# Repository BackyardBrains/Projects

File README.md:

# Projects

Backyard Brains hosts experiment development projects throughout the year. Some of these turn into our experiments, some of these are for our own intellectual curiosity, and some turn into publications in peer reviewed journals. Here you will find each project which contains our open-source schematics, docs, and code.

The projects are:

 * Songbird - A device that can collect environmental and geo-positioning data while detecting and identifying birdsongs automatically.

 * Electric Fish - A collection of projects designed around the recording and micro-stimulation of weakly electric fish. For electric fish that produce "spikes", we are developing a long-term recording device to listen for spiking activity and record the waveforms at highspeed.  For "wave" electric fish, we are developing a device that listens to the frequency of the electric fish, and to initiate a jamming avoidance response by adding an artifical fish in the water next to it that emits a frequency similar to the fish.

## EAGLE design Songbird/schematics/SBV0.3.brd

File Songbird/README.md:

# Songbird project

## Background 

Climate change is affecting all of the natural world, and the habitat and survival of many species of birds are being threatened. In order to understand the effects of climate change on birds, it is crucial to record and track songbird activity. The goal of this project is to develop a system that can correctly identify the songs of eight common and local birds of Michigan. This device will record the bird song and relevant environmental information, such as start time, end time, and location. In doing so, we must consider and further define our goals for power usage, connectivity, longevity, and cost. Our ultimate goal is to create a product that can automatically report this data and is suitable for deployment in nature spanning weeks or months. Our highest level stakeholder, Backyard Brains, hopes that their investment will help us learn more about the behavior of songbirds and the broader implications of climate change.

## Early Research and Results

There are many different types of recording devices that field ornithologists use to record songs and calls, as well as existing algorithms that automatically recognize and identify songs. Based on research into relevant literature, there seem to be many different projects that cover this topic, but our device will be unique in execution. As of now, we plan to either upcycle phones or create our own devices to be placed in the field that will record bird songs.This data will then be processed by the device or stored for processing post recording. Machine learning techniques have shown to be very successful in identifying birds. We have also explored the ideas of using pitch and timbre data and the difference between calls and songs to help us identify bird species. Some challenges that we may face include noise interference, file storage, and durability of the recording devices.

## Impact of Success 

This project is important to our sponsor because bird song and communication is applicable to the field of neuroscience, and birdsongs can tell us much about their behavior. Additionally, Backyard Brains is a company focused on educational outreach, and this project is a good way of educating the public on bird behavior, climate change, and how they can be a part of data collection for research. More broadly, this is important for ornithologists and ecologists because the project provides an accessible and effective device that can provide insight into the patterns of bird populations. Researchers will be able to use this data to use for further studies in understanding the effects of climate change. The device will not be limited to scientists, but be available to the public as well as a way to be involved in community science.

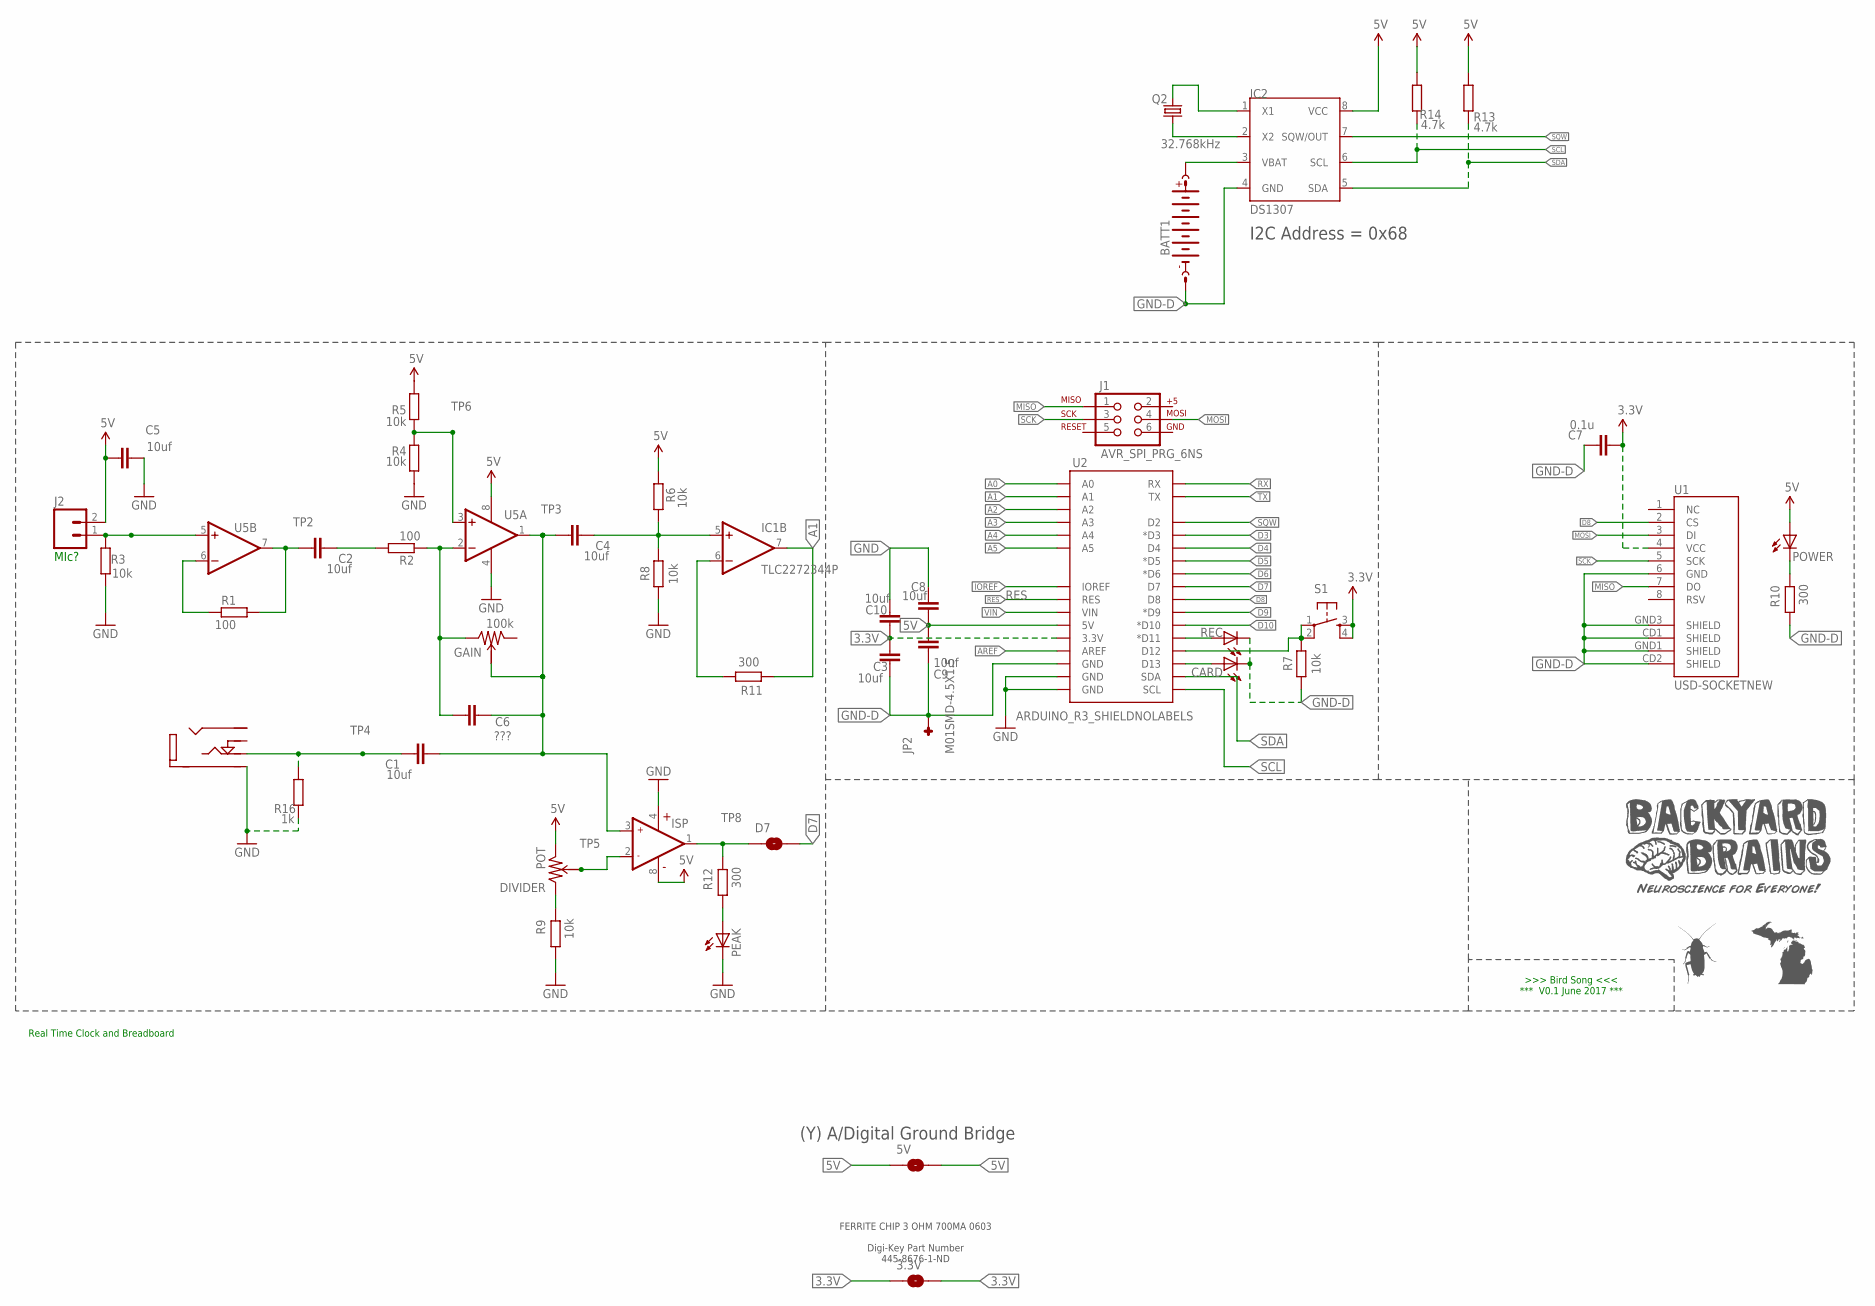
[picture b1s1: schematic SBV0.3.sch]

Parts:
3.3V, 5V: SOLDERJUMPERTRACE; SJ_2S-TRACE
BATT1: BATTERY-16MMSMD; 16M_BATT_SMD
C1, C2, C3, C4, C5, C8, C9, C10: 10uf; M2-CAP; PARTNO K474Z20Y5VE5TL2; DIGIKEY BC1150CT-ND
C6: ???; M2-CAP; PARTNO K474Z20Y5VE5TL2; DIGIKEY BC1150CT-ND
C7: 0.1u; M2-CAP; PARTNO K474Z20Y5VE5TL2; DIGIKEY BC1150CT-ND
CARD: LED5MM
D7: SOLDERJUMPERTRACE; SJ_2S-TRACE
DIVIDER: POT; BURNS-SCREW-POT
GAIN: 100k; BURNS-SCREW-POT
IC1: TLC2272344P; DIL08
IC2: DS1307; DIL08
J1: AVR_SPI_PRG_6NS; 2X3-NS
J2: M02PTH; 1X02
J3: AUDIOJACK; 3.5MM-SMALL-JACK-NEW
JP2: M01SMD-4.5X1.5; PAD-1.5X4.5
PEAK: LED5MM
POWER: LED5MM
Q2: 32.768kHz; TC26H
R1, R2: 100; 0309V; PARTNO CF14JT390R; DIGIKEY CF14JT390RCT-ND
R3, R6, R7, R8: 10k; 0309V; PARTNO ERD-S2TJ102V; DIGIKEY P1.0KBACT-ND
R4, R5, R9: 10k; 0309V; PARTNO CF14JT390R; DIGIKEY CF14JT390RCT-ND
R10, R12: 300; 0309V; PARTNO CF14JT390R; DIGIKEY CF14JT390RCT-ND
R11: 300; 0309V; PARTNO ERD-S2TJ102V; DIGIKEY P1.0KBACT-ND
R13, R14: 4.7k; 0309V; PARTNO ERD-S2TJ102V; DIGIKEY P1.0KBACT-ND
R16: 1k; 0309V; PARTNO ERD-S2TJ102V; DIGIKEY P1.0KBACT-ND
REC: LED5MM
S1: TAC_SWITCHPTH; TACTILE-PTH
TP1, TP2, TP3, TP4, TP5, TP6, TP8: TEST; PROBE_TP
U1: USD-SOCKETNEW; MICRO-SD-SOCKET-PP
U2: ARDUINO_R3_SHIELDNOLABELS; UNO_R3_SHIELD_NOLABELS
U5: TLC2272344P; DIL08; PARTNO TLC2272CP; DIGIKEY 296-1812-5-ND

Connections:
3.3V: 3.3V.1, 3.3V.2, C3.1, C7.1, C10.1, S1.3, S1.4, U1.4 (VCC), U2.3.3V
5V: 5V.1, 5V.2, C5.1, C8.2, C9.2, DIVIDER.1, IC1.8 (V+), IC2.8 (VCC), J2.2, POWER.A, R5.2, R6.1, R13.2, R14.2, U2.5V, U5.8 (V+)
A0: U2.A0
A1: IC1.7 (OUT), R11.2, U2.A1
A2: U2.A2
A3: U2.A3
A4: U2.A4
A5: U2.A5
AMP2: C2.1, R1.2, TP2.P$1, U5.7 (OUT)
AREF: U2.AREF
ASD: D7.1, IC1.1 (OUT), R12.1, TP8.P$1
D3: U2.D3 (*D3)
D4: U2.D4
D5: U2.D5 (*D5)
D6: U2.D6 (*D6)
D7: D7.2, U2.D7
D8: U1.2 (CS), U2.D8
D9: U2.D9 (*D9)
D10: U2.D10 (*D10)
FILTER: C1.1, C4.1, C6.2, GAIN.2, IC1.3 (IN+), TP3.P$1, U5.1 (OUT)
GND: C5.2, C8.1, C10.2, IC1.4 (V-), J3.SHIELD, PEAK.K (C), R3.1, R4.1, R8.2, R9.2, R16.1, U2.GND@0 (GND), U2.GND@1 (GND), U5.4 (V-)
GND-D: BATT1.NEG (-), C3.2, C7.2, C9.1, CARD.K (C), IC2.4 (GND), JP2.P$1, R7.2, R10.2, REC.K (C), U1.6 (GND), U1.CD1 (SHIELD), U1.CD2 (SHIELD), U1.GND1 (SHIELD), U1.GND3 (SHIELD), U2.GND@2 (GND)
IOREF: U2.IOREF
MISO: J1.1, U1.7 (DO)
MOSI: J1.4, U1.3 (DI)
unnamed: J2.1, R3.2, TP1.P$1, U5.5 (+IN)
unnamed: REC.A, U2.D11 (*D11)
unnamed: R1.1, U5.6 (-IN)
unnamed: C2.2, R2.2
unnamed: R4.2, R5.1, TP6.P$1, U5.3 (+IN)
unnamed: POWER.K (C), R10.1
unnamed: DIVIDER.3, R9.1
unnamed: IC2.1 (X1), Q2.2
unnamed: IC1.6 (-IN), R11.1
unnamed: IC2.2 (X2), Q2.1
unnamed: DIVIDER.2, IC1.2 (IN-), TP5.P$1
unnamed: R7.1, S1.1, S1.2, U2.D12
unnamed: CARD.A, U2.D13
unnamed: PEAK.A, R12.2
unnamed: BATT1.POS1 (+), BATT1.POS2 (+), IC2.3 (VBAT)
unnamed: C1.2, J3.R, R16.2, TP4.P$1
unnamed: C6.1, GAIN.3, R2.1, U5.2 (-IN)
PREA1: C4.2, IC1.5 (+IN), R6.2, R8.1
RES: U2.RES
RX: U2.RX
SCK: J1.3, U1.5 (SCK)
SCL: IC2.6 (SCL), R14.1, U2.SCL
SDA: IC2.5 (SDA), R13.1, U2.SDA
SQW: IC2.7 (SQW/OUT), U2.D2
TX: U2.TX
VIN: U2.VIN

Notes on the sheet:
MIc?
I2C Address = 0x68
Real Time Clock and Breadboard
FERRITE CHIP 3 OHM 700MA 0603 Digi-Key Part Number 445-8676-1-ND
(Y) A/Digital Ground Bridge

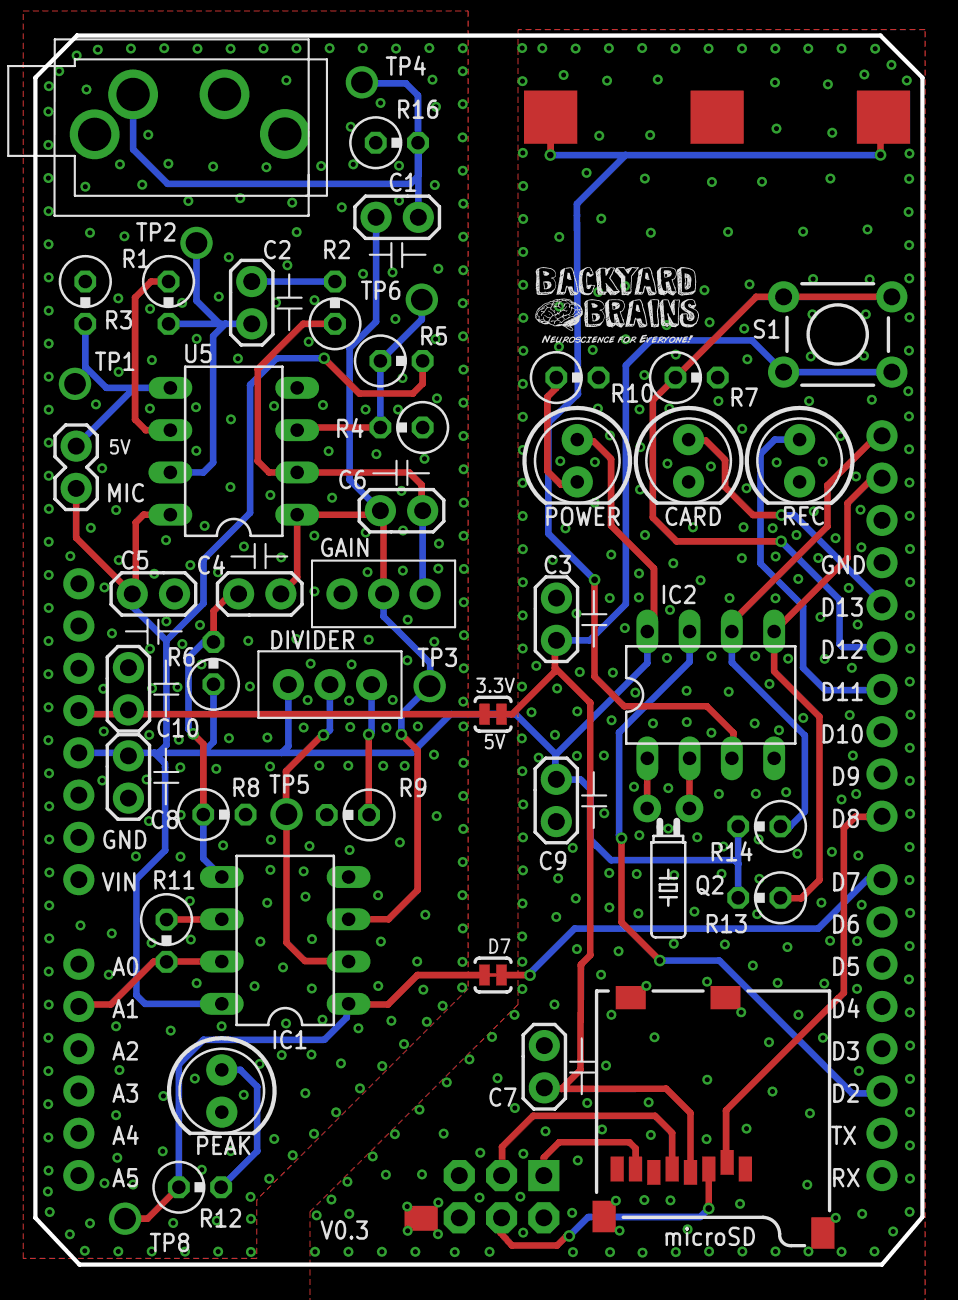
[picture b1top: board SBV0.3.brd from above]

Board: 2 copper layers, 53.3 x 73.9 mm, 54 parts (1 on the bottom side), 34 nets.

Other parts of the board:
U$1: LOGO-NEW-SMALL

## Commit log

2017-02-01 Songbird dir added
2017-02-03 Old projects added to Archive
2017-02-06 Added Directories
2017-02-06 Adding Directores
2017-02-06 Update README.md
    Added descriptions
2017-02-07 Added Electric Fish projects to readme
2017-02-07 Added electric fish descriptions.
2017-02-11 Added files for testing pyaudioanalysis
2017-02-17 added more testing statistics
2017-02-20 fixed divide by zero bug
2017-02-22 unicode fix
2017-02-23 created noise removal function
2017-02-25 added noise removal for entire directory recursively
2017-03-05 database...
2017-03-05 updated database
2017-03-11 logo
2017-03-11 database update to the species and percentage and the variable types
2017-03-11 buttons
2017-03-13 button style
2017-03-13 controllers
2017-03-13 get request and op
2017-03-13 options
2017-03-13 100 lines of random data
2017-03-13 edits
2017-03-13 type not long enough
2017-03-13 data
2017-03-13 changes to get rid of indent?
2017-03-13 quotes
2017-03-14 vagrant
2017-03-15 deleted vagrant
2017-03-15 output precision and style updates
2017-03-15 relative picture size
2017-03-15 more updates
2017-03-21 updates to app layout for easier use/navigation
2017-03-21 added to web app
2017-03-21 got rid of path
2017-03-22 web app update
2017-03-22 navbar
2017-03-22 main is done!
2017-03-28 changed directory name convention to avoid confusion for categorization
2017-03-29 Reverted changes in main.py and index.html, then added other sections. Added working sqlpage. Will need to do input sanitization later to prevent database modifications.
2017-03-29 git ignore
2017-03-29 Sanitized sql command input for sqlpage.
2017-03-29 slight improvements to noise_removal
2017-03-30 basic implementation for processing on device
2017-03-30 bug fixes
2017-03-31 updated for compatability with new version of pysox
2017-04-01 bug fix
2017-04-02 added sanitize, slight tweak to error message in noise_removal
2017-04-02 testing protocol updates
2017-04-02 added sanitize to testing
2017-04-05 updates to web app
2017-04-05 moved css style so that it covers the main page table too
2017-04-05 added categorize file, parrellelized noisered
2017-04-06 bug fix for version mismatch on device
2017-04-06 typo
2017-04-06 compatablity
2017-04-06 device compatability
2017-04-06 added skip-clean option to clean and test and fixed model name bug
2017-04-08 added no-sanitize option
2017-04-09 Added on-device classifier to create sql files to import into live server
2017-04-13 classifier updates
2017-04-18 database folder has been deleted and moved to bybsongbird repository
2017-04-18 added single file classify
2017-04-18 added current model
2017-04-26 parallel classifier v1
2017-04-27 parallelized testing procedure
2017-04-27 added choose number of threads option to objects
2017-04-27 added number of threads option to command line for classifier
2017-05-18 error handling in noise reduce
2017-05-30 some stats analysis
2017-05-31 stats
2017-05-31 test cases
2017-05-31 individual roc curve plotting and auc (hopefully)
2017-05-31 auc should be correct, but don't have graphing yet
2017-05-31 have individual aucs and macro-averaged auc, no curve plotting yet
2017-05-31 possibly all auc measures?
2017-05-31 started realtime recording
2017-06-02 handle weird error
2017-06-04 multithreading workaround for pi zero
2017-06-04 quick noise reduction fix
2017-06-04 error handling
2017-06-04 debug and non-debug for file processing
2017-06-04 fs error fix
2017-06-19 New project for sleep EEG and memory
2017-06-21 changed default detection threshold in test case to 0.5 from 0.7
2017-06-21 test case with no_cat included
2017-06-21 test case update
2017-06-21 test case update - no_cat fix
2017-06-30 Mosquito Love Songs
2017-06-30 First commit of Mosquito project
2017-06-30 Background commit of Mosquito project
2017-07-02 added auto-create db if doesn't exist in classifier object initialization
2017-07-02 added m0 pro code to git repository
2017-07-03 commented out digitalWrite()s used for debugging
2017-07-03 Directory structure added
2017-07-05 added m0 shield schematics
2017-07-05 git ignore added
2017-07-05 Delta Wave Detection Criteria Matlab File Added
2017-07-05 Remove criteria code
2017-07-06 First Release
2017-07-06 First commit of EEG mind reading
2017-07-06 realtime clock
2017-07-07 4.34.34.34.3
2017-07-07 4.41 - Aesthestic Changes
2017-07-07 4.42
2017-07-08 4.43
2017-07-09 4.44
2017-07-10 4.5: Minor Setup Changes and Control Impl.
2017-07-10 4.51: Settings Navigation, Time Bug Fix, Color Scheme Change
2017-07-10 4.52 - Bug fixes
2017-07-10 added sd file toggle to firmware
2017-07-10 slight sd file close fix
2017-07-10 4.53
2017-07-11 4.54 - image resize and position reconfigure
2017-07-11 4.55
2017-07-11 4.56 - Partial Pairs Eliminated, Minor Bug Fixes
2017-07-11 Updated creation of training and test sets
2017-07-12 Test only on Joud's long file
2017-07-12 Ratio changed in NN taining
2017-07-12 Test just Joud
2017-07-13 Analyze Averaged Data
2017-07-13 Grouped Subjects
2017-07-13 noise removal fix for error handling
2017-07-14 missing line
2017-07-14 More Data Analysis
2017-07-15 "new_src" changed to "src"
2017-07-15 Changed name to better reflect that we are creating a database, not the data itself.
2017-07-15 Added Segment Begin and End Timestamps
2017-07-15 Adding plot utilities
    Added utilities subdirectory
2017-07-15 Added new data files
2017-07-15 Added calculations for segments
    Segments are the blocks of picture trials.
2017-07-15 Fixed bug of calculating zscore in segments
2017-07-16 Added function to Generate Session Document
2017-07-16 Linear SVM classification added for face/non-face problem on raw ERP EEG
2017-07-16 Update label on confusion matrix
2017-07-17 newly collected data that require troubleshooting
2017-07-17 more subjects
2017-07-17 Script for runinng of SVN classification added
2017-07-17 Create testRawDataSVMClassificaation
2017-07-17 Create new file
2017-07-17 Corrected the orientation of channels
2017-07-17 Real time sampling from 6ch arduino
2017-07-17 Changed naming of ERPs, standardized prepareSVMData
2017-07-17 Renamed and updated testScript for classification
2017-07-17 modified linear SVM
2017-07-17 SVM made so that we can dinamicaly change size of input vector
2017-07-17 testRawDataSVMClassificaton added
    Run this file to see classification results
2017-07-18 Real time ERP extraction
2017-07-18 Deconding of light sensor information added
2017-07-18 Cleaned up whitespaces
2017-07-18 Real time classification added
2017-07-18 Debug data files removed
2017-07-19 RT recordings from Nathan's test added to DB
2017-07-19 Results of RT classification updated
2017-07-19 Change time window to -100ms to 500ms
2017-07-19 Save of results to mat file added for RT classifier
2017-07-19 Hours minutes and seconds added to name of the RT classification file
2017-07-19 Statistics added at the end of rt classification
2017-07-19 changed behavior of sd toggle button from hold to disable to press to toggle
2017-07-20 Save of training data added
2017-07-20 New data recordings added
2017-07-20 button fix
2017-07-20 Data
    Added data collected
2017-07-20 Zach
    Added data from Zach
2017-07-20 sd-light now goes to the off position if the card isn't detected on boot
2017-07-20 Added Ch6
2017-07-20 Added Spencer'sdata
2017-07-21 New plots and filtering added to EEG decoding
2017-07-21 Changed graphs
2017-07-21 Fixed typo
    weerd -> weird
2017-07-21 Conflict removed
2017-07-21 changes mafe on generateSession
2017-07-22 Real time plot of ERP and image display for predicted class added
2017-07-22 Remove ticks on image output
2017-07-22 Change in graphs in classifier
2017-07-22 mean ERPs added to subplots
2017-07-22 SVM weights added to plot
2017-07-22 testing image added
2017-07-22 Time axis added to SVM wights plot
2017-07-22 Change in axis for 6th channel
2017-07-23 consistency updates
2017-07-23 Basic Home Screen and Save Functionality
2017-07-23 Modified GUI by Greg
2017-07-24 Edits and Recovery
2017-07-24 NewMerge branch 'master' of https://github.com/BackyardBrains/Projects
2017-07-24 Changed the image (correct/incorrect)
2017-07-24 added Christy's data (MR37, MR38)
2017-07-24 Image size changed so that is centered
2017-07-24 Added data collected
2017-07-24 deleted duplicated data
2017-07-24 CommitMerge branch 'master' of https://github.com/BackyardBrains/Projects
2017-07-25 Edit
2017-07-25 various setup fixes
2017-07-25 quick led fix
2017-07-25 Saving Improve
2017-07-25 More Edits for Saving
2017-07-25 Tentatively Fixed Save Function
2017-07-25 minor changes
2017-07-25 Correct conflicts in mind reading
2017-07-25 Added Colors
2017-07-25 Detection of platform added
2017-07-25 added spencer's daata
2017-07-25 added Spencer's third trial with scaling
2017-07-25 Online RT classifier with multiple classes added
2017-07-25 changed code by Greg
2017-07-26 Face/non-face image added
2017-07-26 Blank image added to classification result after 2 sec
2017-07-26 GUI changed to match one from successfull test
2017-07-26 updated new images
2017-07-26 Plot classifier first commit
2017-07-26 Uncomment deploy Classifier
2017-07-26 adjusted images
2017-07-26 changed decoding
2017-07-26 added images
2017-07-26 added imaged face, scene
2017-07-26 coomit
2017-07-26 changed the port
2017-07-26 Visualization of SVN added
2017-07-26 SVM vizualization uses output of SVM and not correct outputs for claster display
2017-07-26 Visualization removed
2017-07-26 added changes
2017-08-01 Visualize SVM data
2017-08-03 README for flyPAD led stimulation
    Initial commit
2017-08-09 Arduino code added to Fruit Fly Optogenetics project
2017-08-09 Readme added to fruit fly project
2017-08-10 Added comments
2017-09-30 Added temp/humidity sensor support, includes values as metadata in wav file
2017-10-01 added temp/humidity automatic support, fixed minor file extension bug, changed humidity to float value, fixed mistake where sampleid was hash of filename instead of file contents
2017-10-01 fixed minor mistake where sql entry is not resubmitted after automatic table creation
2017-10-04 Deleted uncessacary files, various updates / tweaks to model test utility
2017-10-07 Added record led status, fixed bug in stop button, added lat/lon to meta data read from config file
2018-03-30 Visualization for TED for mind reading
2018-03-30 New visualization added for TED video (mind reading)
2019-06-19 Test Flight version 0.9 Build 6

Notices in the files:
parts and their libraries:
SparkFun-Boards: Licensing: CC v3.0 Share-Alike You are welcome to use this library for commercial purposes.
